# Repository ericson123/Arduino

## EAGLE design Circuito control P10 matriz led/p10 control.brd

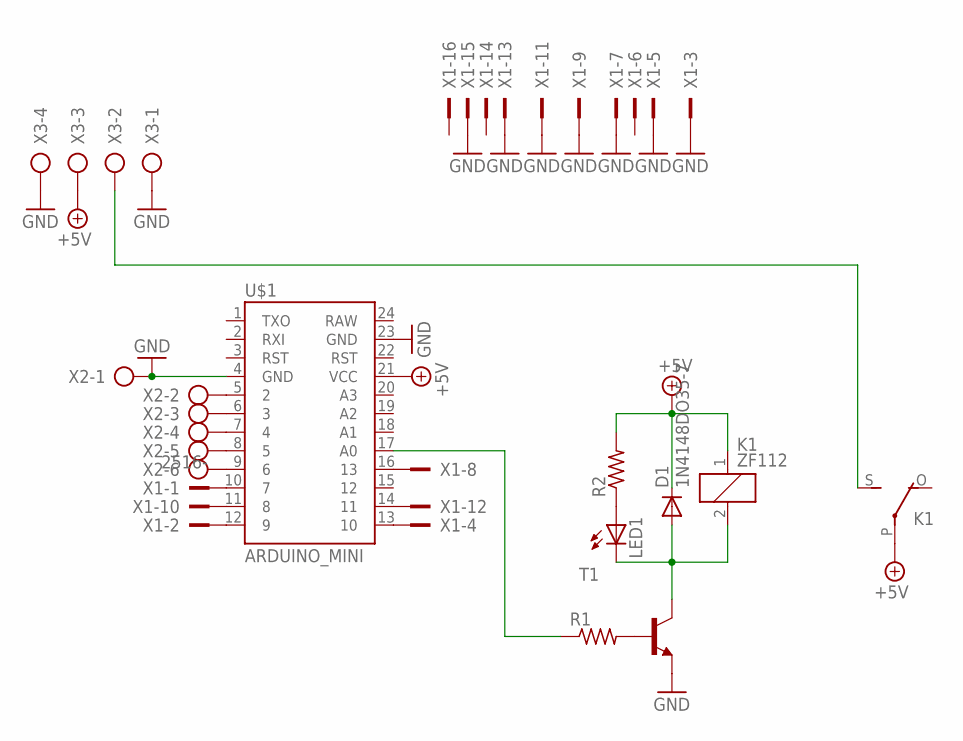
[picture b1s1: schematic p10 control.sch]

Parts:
D1: 1N4148DO35-7; DO35-7
K1: ZF112
LED1: LED3MM
R1: R-US_0207/7; 0207/7
R2: R-US_0207/10; 0207/10
T1: 2N3904-NPN-TO92-EBC; TO92-EBC
U$1: ARDUINO_MINI
X1: 2516-; PAK100/2500-16
X2: AK500/6
X3: AK500/4

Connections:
+5V: D1.C, K1.1, K1.P, R2.2, U$1.21 (VCC), X3.3
GND: T1.E, U$1.4 (GND), U$1.23 (GND), X1.3, X1.5, X1.7, X1.9, X1.11, X1.13, X1.15, X2.1, X3.1, X3.4
unnamed: R1.2, T1.B
unnamed: U$1.13 (10), X1.4
unnamed: U$1.16 (13), X1.8
unnamed: U$1.11 (8), X1.10
unnamed: U$1.14 (11), X1.12
unnamed: U$1.12 (9), X1.2
unnamed: U$1.10 (7), X1.1
unnamed: U$1.9 (6), X2.6
unnamed: U$1.8 (5), X2.5
unnamed: U$1.7 (4), X2.4
unnamed: U$1.6 (3), X2.3
unnamed: U$1.5 (2), X2.2
unnamed: LED1.A, R2.1
unnamed: D1.A, K1.2, LED1.K (C), T1.C
unnamed: R1.1, U$1.17 (A0)
unnamed: K1.S, X3.2

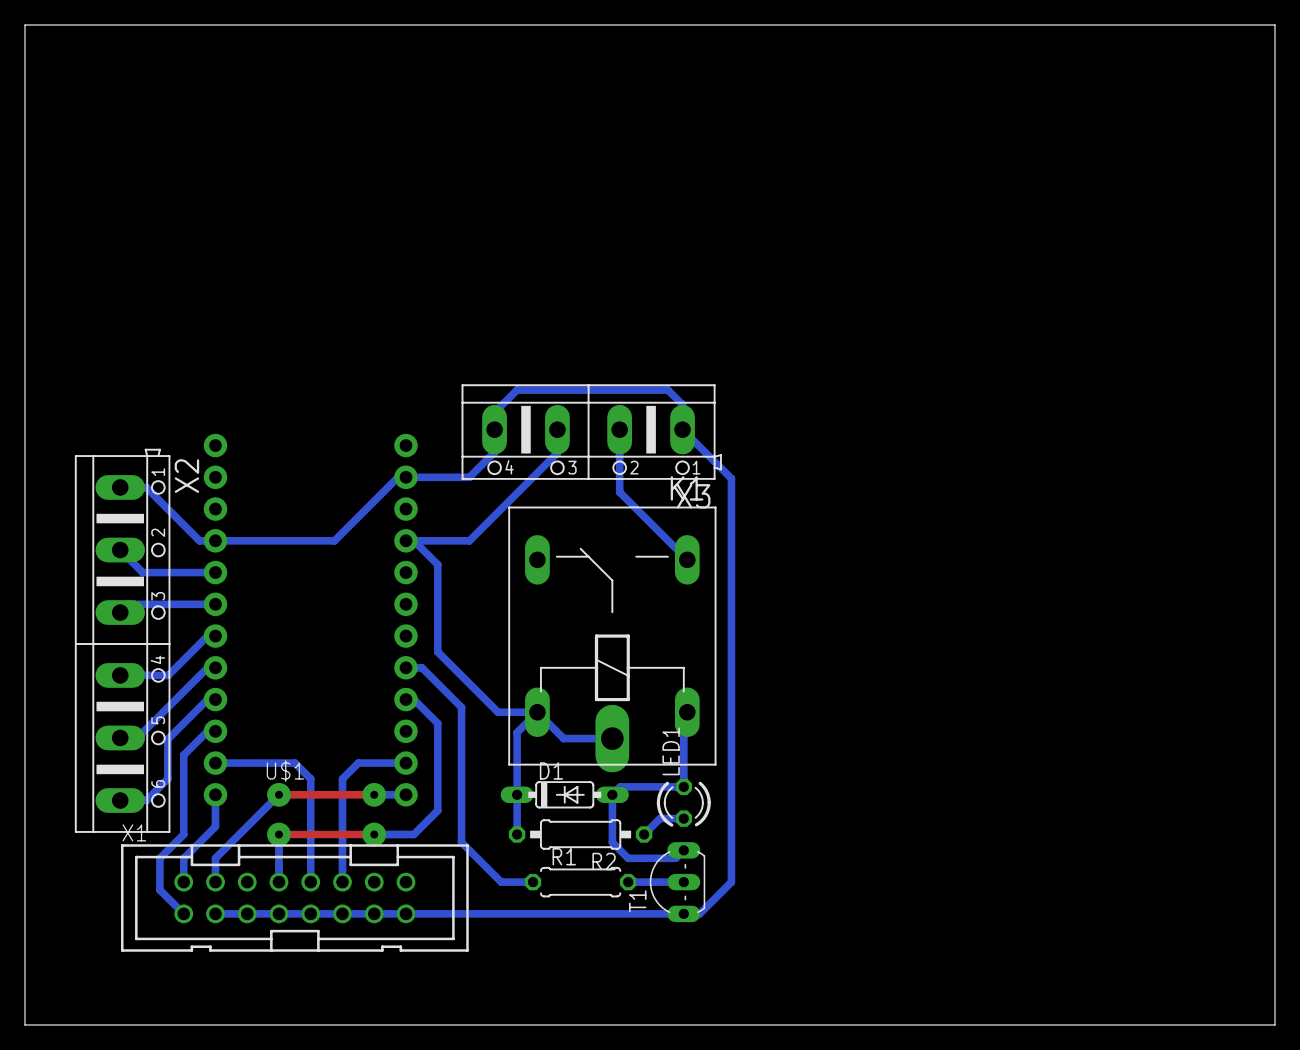
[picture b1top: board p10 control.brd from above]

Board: 2 copper layers, 100.0 x 80.0 mm, 10 parts (0 on the bottom side), 18 nets.

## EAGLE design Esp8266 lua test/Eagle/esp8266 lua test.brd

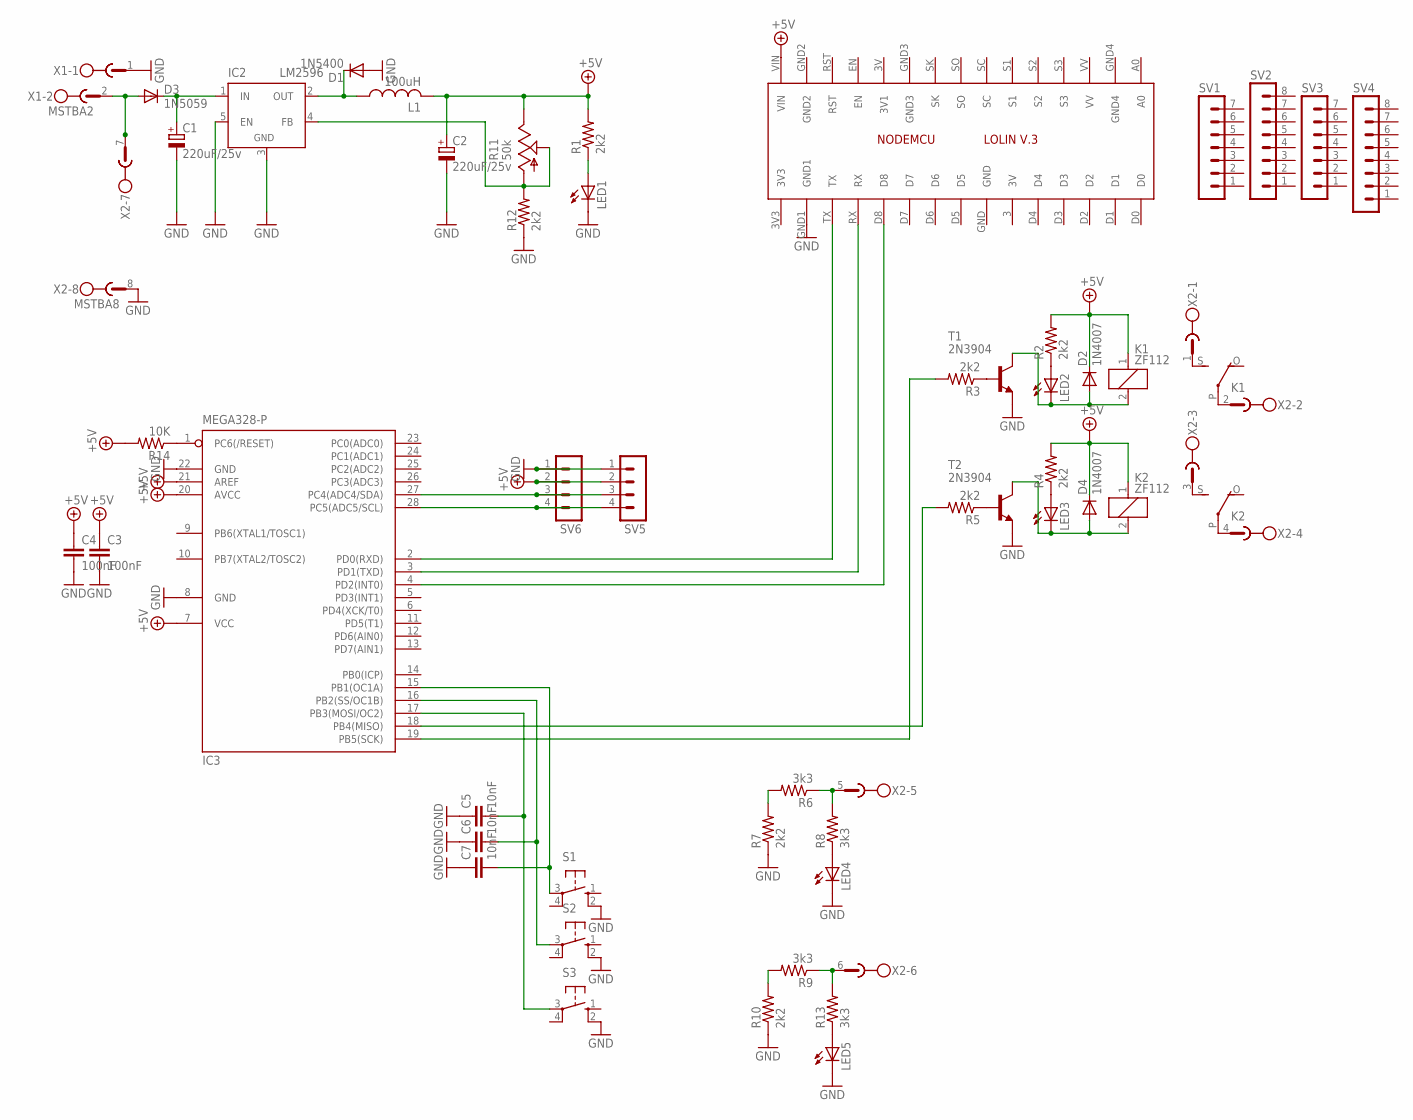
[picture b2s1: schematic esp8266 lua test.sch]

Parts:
C1, C2: 220uF/25v; E3,5-10
C3, C4: 100nF; C050-024X044
C5, C6, C7: 10nF; C050-024X044
D1: 1N5400; DO201-15
D2, D4: 1N4007; DO35-7
D3: 1N5059; DO204-10
IC1: LOLINV3
IC2: LM2596; TO220-51
IC3: MEGA328-P; DIL28-3
K1, K2: ZF112
L1: 100uH; 6000-XXXX-RC
LED1, LED2, LED3, LED4, LED5: LED3MM
R1, R2, R3, R4, R5, R7, R10, R12: 2k2; 0207/10
R6, R8, R9, R13: 3k3; 0207/10
R11: 50k; B25P
R14: 10K; 0207/10
S1, S2, S3: 10-XX; B3F-10XX
SV1, SV3: MA07-1
SV2, SV4: MA08-1
SV5, SV6: MA04-1
T1, T2: 2N3904; TO92-EBC
X1: MSTBA2
X2: MSTBA8

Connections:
+5V: C2.+, C3.1, C4.1, D2.C, D4.C, IC1.VIN, IC3.7 (VCC), IC3.20 (AVCC), IC3.21 (AREF), K1.1, K2.1, L1.2, R1.2, R2.2, R4.2, R11.E, R14.2, SV5.2, SV6.2
GND: C1.-, C2.-, C3.2, C4.2, C5.1, C6.1, C7.1, D1.A, IC1.GND1, IC2.3 (GND), IC2.5 (EN), IC3.8 (GND), IC3.22 (GND), LED1.K (C), LED4.K (C), LED5.K (C), R7.1, R10.1, R12.1, S1.2 (S1), S2.2 (S1), S3.2 (S1), SV5.1, SV6.1, T1.E, T2.E, X1.1, X2.8
unnamed: LED1.A, R1.1
unnamed: C1.+, D3.C, IC2.1 (IN)
unnamed: D1.C, IC2.2 (OUT), L1.1
unnamed: LED2.A, R2.1
unnamed: D2.A, K1.2, LED2.K (C), T1.C
unnamed: K1.S, X2.1
unnamed: R3.1, T1.B
unnamed: LED3.A, R4.1
unnamed: D4.A, K2.2, LED3.K (C), T2.C
unnamed: R5.1, T2.B
unnamed: LED4.A, R8.1
unnamed: R6.1, R8.2, X2.5
unnamed: R6.2, R7.2
unnamed: LED5.A, R13.1
unnamed: R9.1, R13.2, X2.6
unnamed: R9.2, R10.2
unnamed: K1.P, X2.2
unnamed: K2.S, X2.3
unnamed: K2.P, X2.4
unnamed: IC3.1 (PC6(/RESET)), R14.1
unnamed: IC3.19 (PB5(SCK)), R3.2
unnamed: IC3.18 (PB4(MISO)), R5.2
unnamed: C7.2, IC3.15 (PB1(OC1A)), S1.3
unnamed: C6.2, IC3.16 (PB2(SS/OC1B)), S2.3
unnamed: C5.2, IC3.17 (PB3(MOSI/OC2)), S3.3
unnamed: IC1.TX, IC3.2 (PD0(RXD))
unnamed: IC1.RX, IC3.3 (PD1(TXD))
unnamed: IC1.D8, IC3.4 (PD2(INT0))
unnamed: IC3.27 (PC4(ADC4/SDA)), SV5.3, SV6.3
unnamed: IC3.28 (PC5(ADC5/SCL)), SV5.4, SV6.4
unnamed: D3.A, X1.2, X2.7
unnamed: IC2.4 (FB), R11.A, R11.S, R12.2

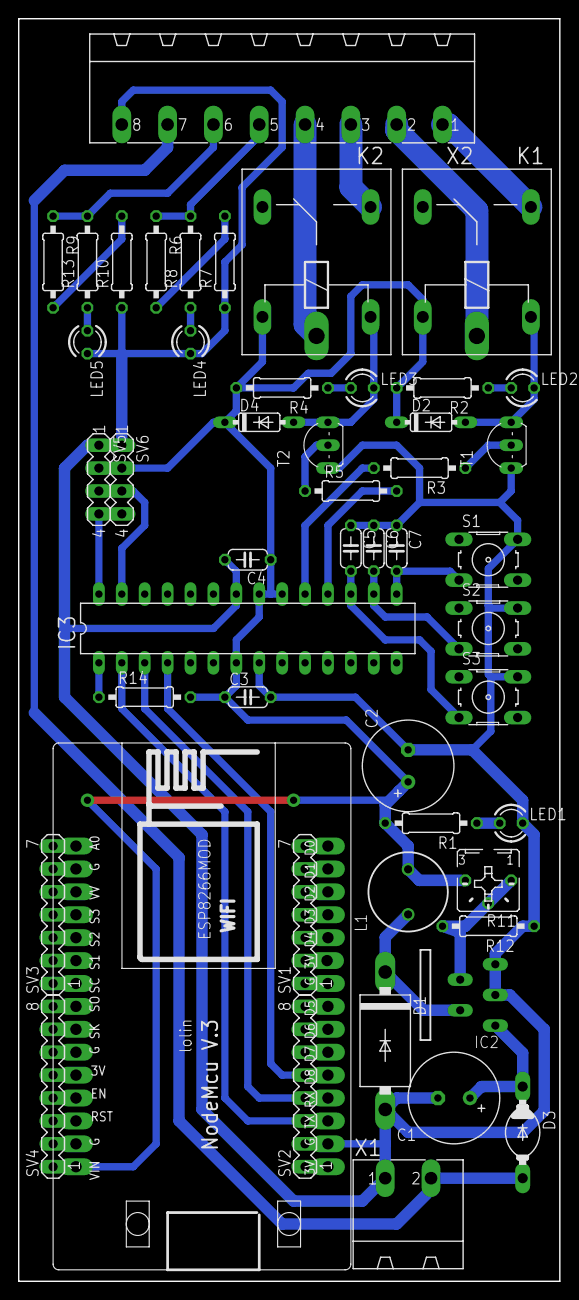
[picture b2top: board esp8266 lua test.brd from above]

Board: 2 copper layers, 60.0 x 140.0 mm, 49 parts (0 on the bottom side), 34 nets.

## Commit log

2020-04-12 hola 1
    hola 2

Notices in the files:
parts and their libraries:
SparkFun-Retired: Licensing: Creative Commons ShareAlike 4.0 International - https://creativecommons.org/licenses/by-sa/4.0
